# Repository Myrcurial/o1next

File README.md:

# o1next

> Rebuilding, upgrading, and eventually recreating the Osborne 1 — research,
> hardware, and the story of how this project began.

A general-purpose Z80 bus interposer for the Osborne 1, built around the RP2354B,
plus the research and reverse-engineering work it enables — and, downstream, a
modern-parts Osborne 1 reproduction (the "O1NEXT").

## The boards

**The shortform is the board's name** — its folder, its site URL and its board id
in `tools/check_schematics.py`. The register, with the state of each one, is
[`hardware/README.md`](hardware/README.md).

| Shortform | Board | Where |
|---|---|---|
| `floppy-adapter` | O1NEXT Floppy Adapter | [`hardware/floppy-adapter/`](hardware/floppy-adapter/) |
| `keyboard-adapter` | O1NEXT USB Keyboard Adapter | [`hardware/keyboard-adapter/`](hardware/keyboard-adapter/) |
| `wifi-comm-pac` | O1NEXT WiFi COMM PAC | [`hardware/wifi-comm-pac/`](hardware/wifi-comm-pac/) |
| `drive-c-repro` | O1NEXT Drive C Repro | [`hardware/drive-c-repro/`](hardware/drive-c-repro/) |
| `interposer-upgrade` | O1NEXT Upgrade — one board in four snap-off sections | [`hardware/interposer-upgrade/`](hardware/interposer-upgrade/) |
| `next-integrated` | O1NEXT Integrated — the SFF board | [`hardware/next-integrated/`](hardware/next-integrated/) |

`O1NEXT Complete` (the machine) is the `next-integrated` board with a case, a
screen, a battery pack and a keyboard — **hardware, but not a board**: chassis CAD,
print STLs, an assembly BOM and its own QMK / Cherry-MX keyboard, all in
`hardware/o1next-complete/`. An LFF 1:1 mainboard is *possible* if a chassis ever
needs restoring, and is not planned.

## What it does

The Osborne 1 places all peripherals in memory-mapped banks and the Z80 has a
simple, slow (4 MHz) external bus. A passive/active interposer in the Z80
socket, connected to an RP2354B, makes the machine both **observable** and
**extensible**:

| Personality | What it does | Code / issue |
|---|---|---|
| **Bus analyzer** (passive) | Cycle-accurate address/data/control capture, streamed over USB — the hardware equivalent of an emulator's machine-state view | `firmware/bus-analyzer/` #17 |
| **Peripheral synthesizer** (active) | Emulates period hardware on the same decode: RT-60A real-time clock, SCREEN-PAC 80/104-column video, IEEE-488 "Drive C" ramdisk/storage, CoPower-88 mailbox | `firmware/*` #18–#24 |
| **CPU emulation shim** | Virtual CoPower-88 (8088), so original SWP software runs on machines without the (rare) physical board | `firmware/copower88-shim/` #23 |
| **Floppy interposer** | Gotek/FlashFloppy analogue: interrupts the Shugart bus and mounts `.IMD`/`.HFE` images to either drive bay, or to "Drive C" as a persistent RAM disk | `firmware/floppy-emulator/` #20 |
| **WiFi modem** | Hayes-compatible AT command set + telnet, presented through the O1's memory-mapped 6850 ACIA registers so period comm programs work unchanged | `hardware/wifi-comm-pac/` #21, #56 |
| **Virtual printer** | Centronics-mode capture on the IEEE-488 port rendered to PDF, emulating a period 9-pin Epson MX-80 | `firmware/virtual-printer/` #19 |

The image library and the printer's PDFs are served by a C64 Ultimate-style
browser UI on the RP2354B, with a CP/M-side utility for in-machine control; no
local mods to the O1 are required (`firmware/web-ui/`).

Electrical/mechanical constraints and the settled design decisions live in
`hardware/README.md` and `firmware/README.md`; the bus and address-space
allocation is in `docs/virtual-peripherals-block-diagram.md`.

## Beyond the interposer — new peripherals for your Osborne 1

The interposer is the centre of the project, but it is not the only way to add
modern capability to the machine. **At least three standalone peripherals** do it
with no interposer, no BIOS change, and nothing cut:

- **USB keyboard adapter (#47)** — RP2040 board on the P4 keyboard connector:
  plug in any USB HID keyboard, no other mods. `hardware/keyboard-adapter/`
- **Severable WiFi modem (#56, #21)** — ESP32 Zimodem fork (telnet + SSH) that
  hangs off the MODEM (P1) port, powers itself from the port, and needs no case
  opened. `hardware/wifi-comm-pac/`
- **Standalone Drive C reproduction (#84)** — RP2040 + flash on the IEEE-488 port
  (P3), powered from the P5 video connector, reproducing the machine's own RAM
  disk. `hardware/drive-c-repro/`

Each attaches to a port the machine already exposes, and each is reversible. The
USB keyboard adapter doubles as the matrix-injection firmware for the
interposer's web-KVM personality (#45).

**One power detail removes the only case-opening step in that list.** The
keyboard adapter's internal variant wants +12 V on P4 pin 19, which means
bridging J6 inside the machine. But the **MODEM port (P1, DE-9 pin 7) carries the
same +12 V through the same R21, and it is reachable without opening anything** —
so a **9-pin passthrough from the keyboard adapter to the modem port** can take
power from there instead. Nobody has to crack the case. Both loads share R21; the
current budget is deferred to `hardware/wifi-comm-pac/README.md`.

Downstream of all of it:

- **O1NEXT (#49, #52)** — modern-parts Osborne 1 reproduction running
  original ROMs and software. **Two boards:** an **LFF board**, a 1:1 mainboard
  replacement for a real **OCC1 or OCC1A** chassis (the restoration path), and an
  **SFF board**, fully integrated and deliberately *not* a 1:1 swap. **The O1NEXT is
  the SFF board with the rest of the machine wrapped around it** — a ~8 cm thick
  portable in O1A blue/grey with an 8" 1024×768 HDMI panel and USB-C PD / 18650
  power; the C64 Ultimate "Crystal" idea applied to an Osborne. `hardware/next-integrated/`
- **Osborne-side software** — MOUNT.COM (#27), FATCOPY (#51), the CoPower-88
  driver (#26) and an updated boot disk (#28): `software/README.md`.

## Status

Phase 0 (research and reverse-engineering, #1) is largely complete and Phase 1
(interposer hardware, #11) has begun — a Rev A schematic exists, but **no board
has been built or tested yet**, so everything downstream of the schematic is
still design work.

Status is deliberately *not* maintained in this file; a status list here goes
stale the day after it is written. The two live sources are:

- **`docs/research-gaps.md`** — every open question, where it stands, and what is
  left to close it.
- **the GitHub issues** — the work itself, one unit per issue, with the doc that
  will carry each result named up front.

The narrative version — how the research actually went, what was surprising, and
the machines it is about — lives on the [Project Blog](https://myrcurial.github.io/o1next/).

## Repository layout

| Path | Holds |
|---|---|
| `research/` | **Sources** — the archive: manuals, schematics, ROMs, disk images and machine photographs, each with recorded provenance (`research/README.md`) |
| `docs/` | **Conclusions** — what we worked out about the Osborne 1, one document per area; index and house style in `docs/README.md` |
| `hardware/` | Device definitions and KiCad projects — interposer, floppy adapter, keyboard adapter, WiFi modem module, O1NEXT (`hardware/README.md`) |
| `firmware/` | On-device firmware, one folder per interposer personality (`firmware/README.md`) |
| `software/` | Osborne-side CP/M software — MOUNT.COM, FATCOPY, CoPower-88 driver, boot disk (`software/README.md`) |
| `tools/` | Disk-image pipeline (TD0 → CP/M filesystem) and host-side analysis scripts (`tools/README.md`) |
| `site/` | The project blog — Jekyll source for GitHub Pages (`site/README.md`) |

## Sources

Full per-file provenance, with source URLs and the archive's licensing note, is
in `research/README.md`. In bulk the raw material comes from bitsavers, Don
Maslin's archive, Dave Dunfield's ImageDisk archive, Brett Hallen's `Osborne_1`
repository, and the Zorba and Kaypro communities.

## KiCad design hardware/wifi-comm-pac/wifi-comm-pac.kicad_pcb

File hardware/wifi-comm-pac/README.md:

# wifi-comm-pac — the O1NEXT WiFi COMM PAC (ESP32 Zimodem fork)

**Board:** `wifi-comm-pac` — the **O1NEXT WiFi COMM PAC** — the project's
**third deliverable**. See the register in [`../README.md`](../README.md).

A Hayes-compatible WiFi modem for the Osborne 1 that closely models the original
Osborne 1 COMM PAC 300-baud modem. It lives in the left-hand floppy storage pocket,
taking power and signal from the MODEM (P1) 9-pin port; the PCB also hosts eleven
indicator LEDs, a 15 × 11 mm speaker, the aux power port for the keyboard adapter,
and a USB-C port for programming or powering the ESP32.

**State: the Rev A schematic is captured; there is no PCB layout yet.**

It is **one design with two physical instantiations** — the standalone COMM PAC in
the machine's floppy pocket, and the same schematic copied onto the interposer and
the SFF board (#323). It is not a daughterboard: the interposer carries its own copy
of the circuit, and only the thing on the far end of GPIO15/16 differs.

Tracks: #56 (extension of #21). Physical interface documented by #57.

## Definition

- **Base:** Zimodem fork targeting **ESP32-S2** (not ESP8266, and not the C-series)
  — the S2 is the variant whose auto-baud pulse counter is **20-bit**, which is what
  makes the machine-side rate detection work at all (#317, #319); it carries the
  SSH client (`INCLUDE_SSH`), and the ESP8266 lacks the headroom entirely.
- **New O1-specific work on top:**
  1. **SSH as first-class transport** — keys, host verification, session
     management via the web UI; `ssh` from the O1 into a modern host.
  2. **Baud-rate buffering/correction** — decouple O1-side ACIA rate
     from the far-end link rate; makes the 2× business turbo (#55)
     usable and quietly corrects the factory 600/2400 → 650/2600 quirk.

## The MCU, the module, and the pin map

**ESP32-S2**, in an **`ESP32-S2-MINI-2U`** module — the **U** for its IPEX/U.FL
connector, which is what lets the antenna go on a pigtail to the case edge, away
from the floppy drives and the CRT (#56 §D).

That is the part Espressif still recommends rather than a preference: the
**MINI-1/MINI-1U are NRND**, and the **WROOM and SOLO/SOLO-U are end of life**
(2025-02-24 and 2024-09-05). The MINI-2 line is what is recommended for new designs.

**The pin map is [`pinmap.md`](pinmap.md)** — fourteen GPIO allocated, the other 23 of
the module's 37 deliberately left free, the panel and the four P1 handshake lines on
two I²C pins, and the fork's `#define` block written out in full. It is **one map for
both roles**: role A and role B differ only in what sits on the other end of
GPIO15/16 (#323).

## Host interface — MODEM port (P1): DE-9 pigtail, 2×5 IDC on the board

**The module does not plug into the machine.** The COMM-PAC sits in the
**left floppy pocket**, a short **10-conductor ribbon** leaves it, and a **DE-9
plug** on the far end goes into the machine's MODEM socket. The board end of
that ribbon is a **2×5 IDC header** — which is why the connector and its
orientation are ours, not inherited (#324). The manual describes it exactly:
*"plug the small, rectangular connector on the modem cable into the 10-pin
socket on the modem… grooved to fit only one way"* (`research/osborne1/Comm-Pac_Users_Manual.pdf`).

Ten conductors carry nine DE-9 signals plus one spare; the original modem used
only six of them (no CTS, no RI), and ours uses all of the status lines.

**TTL levels, not RS-232** — the port feeds the 6850 ACIA directly (status
`2A00H` / data `2A01H`), bypassing the level shifters.

| P1 | Signal | Level | Direction |
|---|---|---|---|
| 1 | GND | — | — |
| 2 | TXD | **5 V TTL** | O1 → module |
| 3 | — | not used | — |
| 4 | MSB | **open-collector** ("50 µA sink = inactive") | module → O1 |
| 5 | CTS | TTL | module → O1 |
| 6 | RXD | **bipolar, −0.5…−10 V = 1** | module → O1 |
| 7 | **+12.6 V DC** | labelled `VDD` in the Comm-Pac manual | power |
| 8 | MCB | TTL, low = suppress output | O1 → module |
| 9 | RI | TTL, falling edge sets the flag | module → O1 |

### The level stage — five signal paths, three part types

**5 V TTL is not 3.3 V, and this board has to say so.** The 6850 and the PIA are
+5 V parts, so TXD and MCB arrive as a 0–5 V swing. The ESP32-S2's input limit
is `VDD + 0.3` — it is **not 5 V tolerant** — so every path below needs level work,
in both directions.

| Path | Part | Why |
|---|---|---|
| TXD, MCB (5 V → 3.3 V) | **74LVC4T245** | dual-supply translator, 5 V-tolerant B side |
| CTS, RI (3.3 V → 5 V) | **74LVC4T245** | the second 4-bit half; one `DIR` per package, so mixed directions cost two packages, not one |
| MSB (3.3 V → open-collector) | **74LVC1G07** | open-drain, 5 V-tolerant output; a push-pull driver would violate the interface |
| RXD (3.3 V → bipolar) | **MAX3232 at 3.3 V** | on-chip charge pump gives **±5.5 V**, inside the machine's −0.5…−10 V window and under the 5.1 V clamp; at 5 V it would swing ±9–10 V, needlessly close to both limits |

The MAX3232's receivers are RS-232-threshold and must **not** be used for the
TTL lines. Its 3.3 V rail is taken **after** the diode-OR, so an unpowered board
can never drive the machine's RXD.

Still to confirm in hardware: the **RXD negative swing**, on a real machine (#324).

## Power

**DE-9 pin 7 is +12.6 V DC, and it is behind the 22 Ω.** The Technical Manual
§4.3.2 says so in words — "7 +12v — Connected to power supply through 22 ohms" —
and sheet 7 of 9 shows the arrangement: `R21 = 22 Ω` hangs off the `+12V` rail and
its lower end is a junction feeding **both** P1 pin 7 and **`J6 pin 1 → J6 pin 2
→ P4-19`**, the keyboard branch.

The sheet labels that node `+12V`, which is what makes this easy to get wrong:
old schematics name a current-limited net after the rail it comes from, so **the
series part sits upstream of the label, and a net label does not tell you where
it is**. A 600 dpi read of the sheet alone does not settle it; the manual is the
tie-breaker, and it says *through 22 ohms*.

**That makes the port current limited, and the limit is the resistor's own rating.**
The sheet's default is **1/4 W** and nothing calls `R21` out, so the continuous
budget is **~107 mA** — 2.35 V dropped, 10.25 V left at the module. (150 mA would
be 0.495 W, a 1/2 W part sitting *at* its rating.) The keyboard adapter (#47)
shares the resistor, so the budget is shared.

**Two ways to be powered, and the choice is open (#356):**

- **(a) Off P1's rail**, under that ~107 mA, with a **large bulk capacitor**
  carrying the burst power. Radio TX is very uneven — long idle, short spikes — so
  the cap supplies the peak and `R21` the average.
- **(b) Off the monitor jack (P5)**, essentially the way `drive-c-repro` will: that
  rail is **not limited** (#354), so the peaks stop being a design problem at the
  cost of a second cable and a shunt.

Either way the board needs a **front-panel interlink connector — a 2×2 keyed IDC
carrying 5 V, 12 V and ground** (`../README.md`, #356) — and a **cuttable trace on
its 12 V input**, so the same PCB is fed either from the machine's video port or
from the link. Its **interlink input is reverse-voltage protected**, and the **keyed
2-pin shroud is the 12 V source end**. If option (a) is refused, the modem
connector's **12 V pin is left disconnected** and the 12 V arrives over the link
instead.

- **Bulk capacitance is doing real work, not tidiness.** A WiFi TX burst is a few
  hundred mA; `R21` cannot supply that, so the capacitor supplies the peak and
  `R21` supplies the average. Size the cap from the burst energy, and check the
  average draw against the shared budget — with 22 Ω in the path there *is* an
  inrush and peak problem to design around.
- **Buck 12.6 V → 5 V**, then **5 V → 3.3 V**; USB-C VBUS is **5 V → 3.3 V only**.
  Two sources, **diode-OR** (Schottky pair, or a P-FET ideal diode if the drop
  matters) so neither back-feeds the other.
- **Switch ahead of the buck**, latching slide type, so "off" is genuinely dark.
  USB still runs the board with no machine attached (bench-prep, #207).
- The machine's `−12 V` rail is rated **0.1 A**; the negative rail for RXD comes
  from the MAX3232's own charge pump, never from the machine.

## Panel

**Eleven lamps and the handshake, on I²C — two AW9523B, split by function.**
U6 (`0x58`) carries the lamps; U7 (`0x59`) carries the four P1 handshake lines.
Both are fitted, because the handshake is not optional: 16 channels each, 5 and
12 spare respectively, and the pin argument is closed for good.

- 8 lamps on **P0** — push-pull, constant-current, per-LED dimming.
- 3 lamps on **P1** (TR, MR, RI) — **P1 is open-drain only** on this part, so
  those three get series resistors and sink from 3.3 V.
- The handshake sits on the 3.3 V side of the translators: CTS and RI out,
  MSB through the `1G07`, MCB in.

The expander **holds its outputs**, so a hung firmware leaves a readable frozen
panel rather than a dark one. Two **INTN** lines go to GPIO38 and GPIO21, and
`RESETN` is strapped with an RC (or shares one GPIO).

LED states and semantics are #322; current is set to **2–3 mA** per lamp.

## Audio

An **I²S-input class-D amplifier with its own DAC** (MAX98357A class) on the
**5 V** rail, three pins (BCLK/LRCLK/DIN) plus gain/mode straps, driving a
**real speaker** — not a piezo buzzer, and not an active buzzer. Both are the
wrong part: an active buzzer knows one note, and a bare piezo element is
non-linear and thin across the band, where the panel has to make **the noise a
modem makes**.

**J2 is Same Sky CMS-151103-088SP** — 15 × 11 × 3 mm rectangular frame, 0.7 W
(1.0 W max), **8 Ω**, PEEK cone, Nd-Fe-B magnet, solder-pad terminals. **8 Ω is the
only number that matters** — it is the load the MAX98357A wants — and the part is
small enough for the floppy-pocket envelope. Pin 1 is the **`+`** terminal (the
datasheet's polarity: the cone moves forward with positive dc on `+`), so it takes
`SPK_P`.

**Audio quality is explicitly not a requirement.** The panel is a noise generator:
it has to make dial tone, DTMF and a ring cadence, and nothing more. It runs in
**free air** in an unsealed case with a perforated front panel — no chamber, no
gasket, no port — and no response curve, resonance or SPL figure is designed
around. The datasheet's Fo and SPL are 1 cc-box measurements and are deliberately
not repeated here as if they described this board.

Its footprint is ours (`o1next:Speaker_SameSky_CMS-151103-088SP`), and its geometry
comes off the datasheet's mechanical drawing: the 15 × 11 × 3 mm body, and **two
0.6 mm square solder pads on the left and right sides**. They are drawn 14.4 mm
apart, with each pad's outer edge flush with the 15 mm body end — that flush
offset is the one number read rather than stated, and it is what would change if
the drawing insets them. **The piezo route is closed, not deferred:** the Multicomp
Pro MCKPT-G1340-3917 buzzer is not fitted, and its footprint is not on the board.

Dial tone, DTMF and ring cadence are in #322; prior art is `na103/zimodem`
(CC BY 4.0 — method only).

## The schematic — two directories

**Two directories, and the generator writes into only one of them.**

| | |
|---|---|
| `wifi-comm-pac-generated/` | the generator's output. Regenerated at will. |
| `wifi-comm-pac-edited/` | the copy a person works on. Never written by the generator. |

`gen_wifi_comm_pac_sch.py` is the **first take** — the mathematical proof that the
circuit is what the netlist says it is. It is not a finished drawing and it cannot
be one: turning it into something a person can read and work on takes a person.
So both exist, and the rule between them is one line:

> if `-edited/` holds a schematic, **the copy is aborted** and the generator says
> so; if `-edited/` is empty, the generated schematic is copied across.

A regeneration therefore cannot overwrite anybody's work, and the first person to
pick the board up gets a starting point without running anything. To deliberately
re-seed, empty `-edited/` first — which discards what is in it.

`tools/check_schematics.py` asserts the **generated** file: the invariant nets
(which P1 pin carries which signal, that the machine's 5 V never reaches a 3.3 V
pin, that the 12.6 V rail stops at the buck), that no symbol or label collides,
that no symbol pin is without a footprint pad, and that the file matches a fresh
regeneration.

### Four sections, and parts sit next to what they connect to

The sheet is A1 (841 × 594 mm) divided into four regions, because the complaint a
reader actually has is not that things are unconnected — it is that they are
connected *across the page* and so cannot be followed:

| Section | Holds |
|---|---|
| **POWER** (bottom band) | the P1 12.6 V rail and the USB-C front end — diode-OR, buck, LDO, polyfuse, the CC pulldowns, the ESD clamp, and the 5 V out |
| **LOGIC** (left, upper) | J1, the level stage, the ESP32 and its support parts, both expanders, and the free-GPIO header |
| **PANEL** (right, upper) | the 11 lamps, one row each: resistor and LED side by side |
| **AUDIO** (right, lower) | the MAX98357A and the speaker |

### The free-GPIO header, J4 — and why it is 2×13

U5 leaves **26 GPIO** unused. No-connect is correct but *terminal*: the pad is on
the module's footprint, the header is not, and reaching it later means redoing the
board. **J4** brings all 26 out to a **2×13 header** — 2×13 exactly, because that
is the 26 GPIO and not 2×14 with grounds.

**It is left unpopulated, and marked `dnp`** so KiCad keeps it out of the BOM and
off the placement file. That is the difference between "left unfitted on purpose"
and "we forgot to order it". The pads cost nothing and mean somebody can solder a
header on later and use the radio, the DACs, the touch channels and the second SPI
set without touching U5's footprint.

Pins are numbered the way a 2×13 is — odd on row 1, even on row 2 — and **named
with the module's own IO names**, so the silk says `IO43` and that is UART0 TXD
without a datasheet lookup:

| | row 1 (odd) | row 2 (even) |
|---|---|---|
| | IO0 IO1 IO2 IO3 IO4 IO5 IO6 IO7 IO8 IO9 IO10 IO11 IO12 | IO13 IO14 IO17 IO18 IO26 IO39 IO40 IO41 IO42 IO43 IO44 IO45 IO46 |

One table in the generator builds U5's symbol, names these nets, *and* labels the
header, and `check_schematics.py` asserts each of the 26 as an **exact pair** — one
U5 pad and one J4 pin. Three separate lists would drift, and the first thing to
drift would be a header pin labelled `IO18` that is really `IO17`, which is the
worst possible bug on a header a hobbyist is meant to use.

### 5 V out to the keyboard adapter

**J5** is a **JST PH, side entry, SMD** (`S2B-PH-SM4-TB`). It is fully shrouded
with a polarising slot, so the plug cannot go in the wrong way round and **there is
no reverse-voltage case to design for**. Side entry means the cable leaves parallel
to the board, straight out the front of the floppy pocket. 2 A, 100 V, 2.0 mm
pitch; KiCad carries the footprint, so nothing is drawn here.

It is fed from the **diode-OR output** (`+5V`), so whichever source is present —
the machine's 12.6 V through the buck, or USB VBUS — feeds the port. That is what
lets the keyboard adapter drop its 12 V→5 V buck and keep only its LDO.

**U11 is the current limit on it.** `D13`/`D14` are SS14 — **1 A each** — so the
5 V rail cannot source more than about an amp, and a port labelled "5 V out"
invites somebody to plug in a load that wants three. `U11` is a **TPS2553**
current-limited power-distribution switch, and `R28` sets the limit: `I_OS = 25.6 /
R_ILIM`, so **27 kΩ gives about 0.95 A** — under the diodes, and 15× the ~60 mA the
adapter draws. It limits rather than latches, so nothing needs to know when it
does; `FAULT` is unused for that reason.

### ESD on the USB-C input

**`D15`** is a `PESD5V0S1BA` on `VBUS_IN`, upstream of the diode-OR, so it is the
first thing a transient meets. 5 V standoff, so it does not conduct on a 5.25 V
VBUS, and it clamps low enough not to overstress the `AP2112K` downstream. The
port is *meant* for a computer; "meant for" is not a protection.

### The wiring, and the defect it fixes

Every signal net is drawn as orthogonal wire segments; the rails use power
symbols; every pin ends on a wire, a power symbol, or a deliberate no-connect
marker. Nothing floats — the generator fails loudly if a pin does.

The router builds a **spanning tree** per net (each pin joined to the nearest
point already on the net, so branches share a trunk) and then **normalises** the
result: every segment is split wherever any point of the same net lies on it, the
duplicates that leaves are dropped, and a junction is placed wherever three or
more wire ends meet.

That normalisation is not cosmetic, and it is the answer to a real failure. The
earlier **star** router drew each pin back to the first pin, which produced
**overlapping collinear segments** — 15 of them, plus 2 exact duplicates. KiCad
tolerates that until it saves the file, at which point its own cleaner normalises
the geometry, and pins that had been attached *only* by sitting inside an overlap
come adrift, because a pin in the middle of a wire is not connected without a
junction. That cost **14 pins across 10 nets** the first time anybody opened the
sheet in KiCad. **A wire KiCad would rewrite is a wire drawn wrong**, so the
generator now does the normalisation itself.

It is checked, not asserted: `kicad-cli sch upgrade` re-saves the schematic in the
current format — the operation that detaches pins from an overlapping drawing — and
the netlist before and after is identical (70 nets, 248 nodes, 0 single-node nets,
317 wires and 8 junctions unchanged).

```sh
python3 hardware/wifi-comm-pac/gen_wifi_comm_pac_sch.py
python3 tools/check_schematics.py --board wifi-comm-pac
```

| Ref | Part | Why |
|---|---|---|
| J1 | 2×5 IDC | the P1 pigtail; pin *n* = DE-9 pin *n* |
| U1, U2 | 74LVC4T245 | 5 V ↔ 3.3 V, one package per direction |
| U3 | 74LVC1G07 | MSB, open-drain only |
| U4 | MAX3232 | RXD, bipolar, on 3.3 V |
| U5 | ESP32-S2-MINI-2U | the modem |
| U6, U7 | AW9523B ×2 | panel (0x58) and handshake (0x59) |
| U8 | MAX98357A | I²S class-D audio |
| U9, U10 | TPS54331, AP2112K | 12.6 V → 5 V → 3.3 V |
| D13, D14 | Schottky pair | the diode-OR between the port and USB |

**Footprints are all assigned** — **71 of 71** component symbols carry one, so
`Update PCB from Schematic` transfers every part rather than nothing.

**But the board is not yet correct, and this is the first layout task.** The
**multi-pin ICs' pin numbers are logical placeholders**, not the vendor packages'.
They exist so the netlist checker can name a pin. The footprints are real; the
pin↔pad correspondence is not. **U5 is the dangerous one:** its symbol has 18
pins numbered 1–18, the `ESP32-S2-MINI-2U` footprint has 73 pads numbered 1–65
plus `61_1`…`61_9`, and the numbers *collide by name* while disagreeing in
meaning — symbol pin 1 is `+3V3`, the module's pin 1 is **`GND1`**. So a transfer
today puts 3.3 V on a ground pad. The other multi-pin parts are merely incomplete
rather than wrong: U1/U2 (9 pins against 16 pads, two of four channels modelled),
U8 (9 against 17), U3 (5 against 6), U6/U7 (24 against 25 — pad 25 is the exposed
pad), SW1 (2 against 7 — the five mounting tabs). U4, U9 and U10 are exact.

**J3 is the exception** that shows the fix: it uses the part's own numbers
(A1–A12, B1–B12, SH1–SH6) because its footprint has 30 pads and every one of them
needed a net. Doing the same for the others means binding each signal to a real
module pin, which is a **GPIO allocation decision** for U5 rather than a datasheet
lookup.

The RXD swing is the remaining hardware confirmation (#324), and the **2×5 IDC
orientation is settled** — see `pinmap.md` §"Open before layout": right-angle and
shrouded, pin 1 on the left facing it, key down toward the PCB.

## Enclosure

The case STL is **already designed and fit-tested** by the maintainer; the
apertures it currently cuts are **USB-C** and the **2×5 IDC**. Final placement,
left to right looking at the front of the machine:

1. **antenna connector** — RP-SMA bulkhead (reverse-polarity, as every WiFi
   pigtail is; the module end is U.FL), fed from the MINI-2U's IPEX connector
2. **power switch**
3. **2×5 IDC** — the P1 ribbon
4. **LED row** — 11 × 3528 with light pipes
5. **USB-C**

The schematic fixes the parts; the placement drawing that goes with it is what
lets the STL be finalised (#56 §E).

## References

- `pinmap.md` — the MCU, the module, and every GPIO
- `docs/o1-modem-serial.md` (authoritative pinout + levels)
- `docs/o1-memory-io-map.md` §"6850 ACIA detail"
- `hardware/interposer-upgrade/` — the interposer the module docks to (#323)
- Upstream: https://github.com/bozimmerman/Zimodem

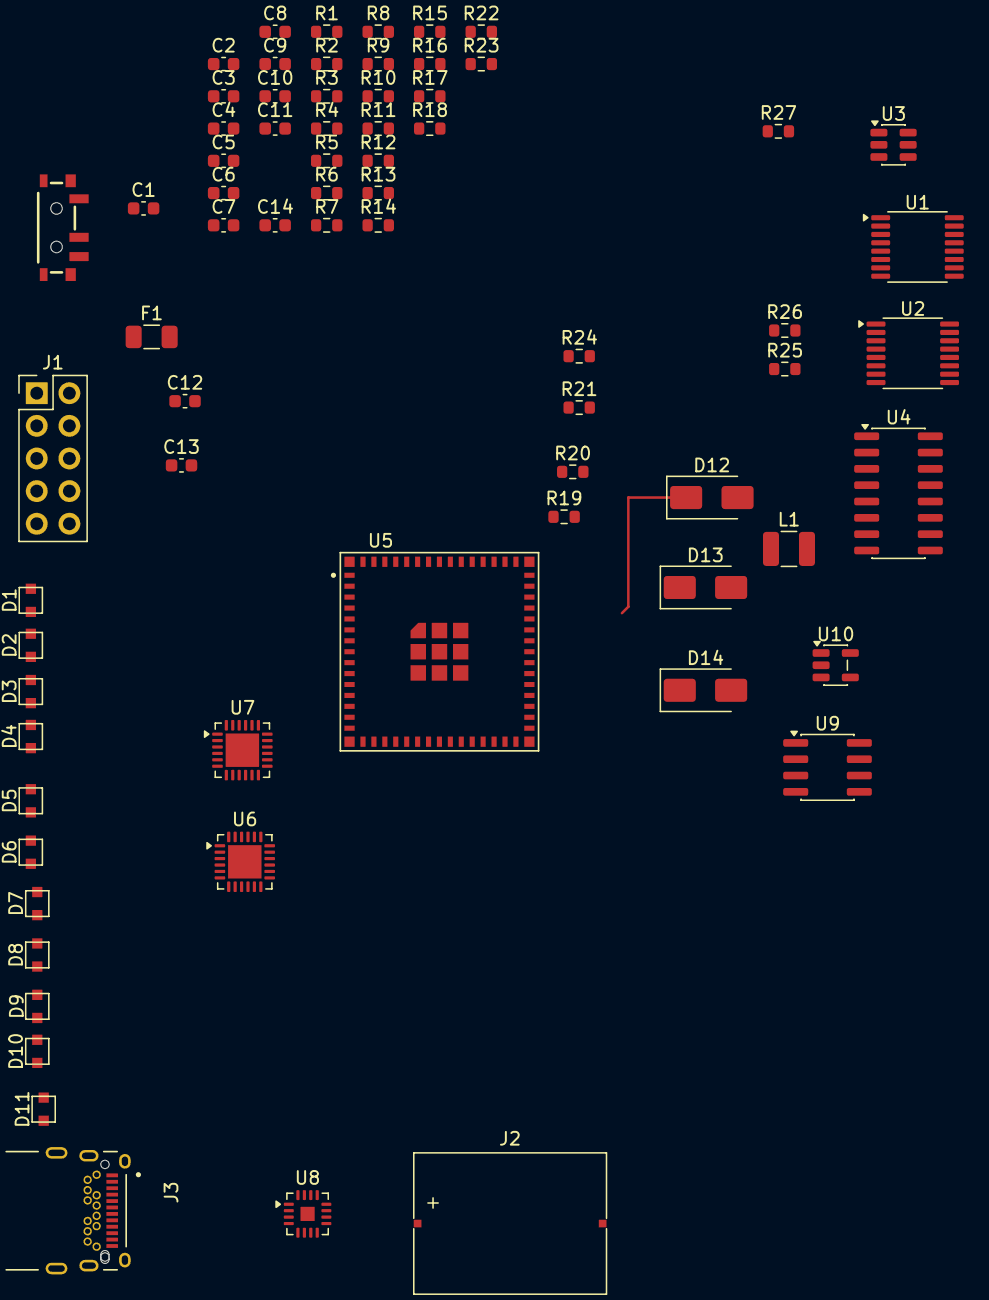
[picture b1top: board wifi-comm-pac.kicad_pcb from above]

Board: 2 copper layers, 71 parts (0 on the bottom side), 70 nets.

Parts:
C1: 220u; C_0603_1608Metric
C2, C8, C9, C10, C11, C12, C14: 100n; C_0603_1608Metric
C3: 10n; C_0603_1608Metric
C4: 1n; C_0603_1608Metric
C5, C6: 22u; C_0603_1608Metric
C7: 10u; C_0603_1608Metric
C13: 1u; C_0603_1608Metric
D1, D2, D3, D4, D5, D6, D7, D8, D9, D10, D11: 3528; LED_SunLED_XZM2CRK168WA
D12: SS34 catch; D_SMA
D13, D14: SS14 OR; D_SMA
F1: polyfuse 1A; Fuse_1206_3216Metric
J1: Conn_02x05 IDC (P1 MODEM); PinHeader_2x05_P2.54mm_Vertical
J2: CMS-151103-088SP; Speaker_SameSky_CMS-151103-088SP
J3: USB-C sink; USB_C_SameSky_UJ32-C-H-G-DSMT-1-P24-TR
L1: 10uH; L_1210_3225Metric
R1, R2, R3, R4, R5, R6, R7, R8, R9, R10, R11: 470R; R_0603_1608Metric
R12, R14, R19, R22, R23, R24, R25, R26, R27: 10k; R_0603_1608Metric
R13: 1k91; R_0603_1608Metric
R15, R16: 5k1; R_0603_1608Metric
R17, R18: 22R; R_0603_1608Metric
R20, R21: 4k7; R_0603_1608Metric
SW1: Slide switch, latching; Slide_SPST_SMD_6.7x2.6mm
U1: 74LVC4T245 (TXD/MCB); TSSOP-16_4.4x5mm_P0.65mm
U2: 74LVC4T245 (CTS/RI); TSSOP-16_4.4x5mm_P0.65mm
U3: 74LVC1G07 (MSB); SOT-23-6
U4: MAX3232 (RXD); SOIC-16_3.9x9.9mm_P1.27mm
U5: ESP32-S2-MINI-2U
U6: AW9523B panel 0x58; QFN-24-1EP_4x4mm_P0.5mm_EP2.6x2.6mm
U7: AW9523B interface 0x59; QFN-24-1EP_4x4mm_P0.5mm_EP2.6x2.6mm
U8: MAX98357A; VQFN-16-1EP_3x3mm_P0.5mm_EP1.1x1.1mm
U9: TPS54331 buck 12.6->5; SOIC-8_3.9x4.9mm_P1.27mm
U10: AP2112K-3.3 LDO; SOT-23-5

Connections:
+3V3: C7.1, C12.1, D9.1, D10.1, D11.1, R19.2 (2_2), R20.2 (2_2), R21.2 (2_2), R22.2, R23.2, R24.2 (2_2), R25.2, R26.2, R27.2, U1.1 (VCCA), U2.1 (VCCA), U2.7 (DIR), U3.5 (VCC), U4.16 (VCC), U5.1 (3V3), U6.1 (VDD), U7.1 (VDD), U7.5 (AD0), U8.6 (SD_MODE), U10.4 (VOUT)
+5V: C6.1, D13.2, D14.2, U1.13 (VCCB), U2.13 (VCCB), U8.1 (VDD), U10.1 (VIN), U10.3 (EN)
+5V_P1: C5.1, D13.1, L1.2, R12.1 (1_1)
+5V_USB: D14.1, F1.2
+12V: J1.7 (+12.6V), SW1.1
+12V_SW: C1.1, SW1.2, U9.2 (VIN), U9.3 (EN)
/BOOT_N: C2.1, U9.1 (BOOT)
/C1N: C8.2, U4.3 (C1-)
/C1P: C8.1, U4.1 (C1+)
/C2N: C9.2, U4.5 (C2-)
/C2P: C9.1, U4.4 (C2+)
/COMP_N: R14.1, U9.6 (COMP)
/ESP_EN: C13.1, U5.3 (EN)
/EXP_RSTN: C14.1, U7.8 (RESETN)
/FB_N: R13.1, U9.5 (VSENSE)
/I2C_SCL: U6.4 (SCL), U7.4 (SCL)
/I2C_SDA: U6.3 (SDA), U7.3 (SDA)
/I2S_BCLK: U5.9 (IO35), U8.3 (BCLK)
/I2S_DIN: U5.11 (IO37), U8.5 (DIN)
/I2S_LRCLK: U5.10 (IO36), U8.4 (LRCLK)
/IF_CTS: R25.1, U2.3 (A1), U7.9 (P1_0)
/IF_MSB: R27.1, U3.2 (A)
/IF_RI: R26.1, U2.4 (A2)
/INT_IF: R23.1, U7.7 (INTN)
/INT_PANEL: R22.1, U5.12 (IO38)
/LED_AA: R4.1, U6.20 (P0_3)
/LED_AA_A: D4.1, R4.2
/LED_CD: R5.1, U6.21 (P0_4)
/LED_CD_A: D5.1, R5.2
/LED_CONN: R2.1, U6.18 (P0_1)
/LED_CONN_A: D2.1, R2.2
/LED_HS: R3.1, U6.19 (P0_2)
/LED_HS_A: D3.1, R3.2
/LED_MR_A: D10.2, R10.2
/LED_MR_K: R10.1, U6.10 (P1_1)
/LED_OH: R6.1, U6.22 (P0_5)
/LED_OH_A: D6.1, R6.2
/LED_RADIO: R1.1, U6.17 (P0_0)
/LED_RADIO_A: D1.1, R1.2
/LED_RD: R7.1, U6.23 (P0_6)
/LED_RD_A: D7.1, R7.2
/LED_RI_A: D11.2, R11.2
/LED_RI_K: R11.1, U6.11 (P1_2)
/LED_SD: R8.1, U6.24 (P0_7)
/LED_SD_A: D8.1, R8.2
/LED_TR_A: D9.2, R9.2
/LED_TR_K: R9.1, U6.9 (P1_0)
/O1_MCB_3V3: U1.4 (A2), U7.12 (P1_3)
/O1_TXD_3V3: U1.3 (A1), U5.6 (IO16)
/P1_CTS: J1.5 (CTS), U2.8 (B1)
/P1_MCB: J1.8 (MCB), U1.9 (B2)
/P1_MSB: J1.4 (MSB), U3.4 (Y)
/P1_RI: J1.9 (RI), U2.9 (B2)
/P1_RXD: J1.6 (RXD), U4.14 (T1OUT)
/P1_TXD: J1.2 (TXD), U1.8 (B1)
/PH_N: C2.2, D12.2, L1.1, U9.8 (PH)
/SPK_N: J2.2, U8.9 (OUT-)
/SPK_P: J2.1, U8.8 (OUT+)
/SS_N: C3.1, U9.4 (SS)
/UART1_TX: U4.11 (T1IN), U5.5 (IO15)
/USB_CC1: J3.A5 (CC1), R15.1
/USB_CC2: J3.B5 (CC2), R16.1
/USB_DM_CON: J3.A7 (DN1), J3.B7 (DN2), R18.2
/USB_DM_ESP: R18.1, U5.14 (IO19)
/USB_DP_CON: J3.A6 (DP1), J3.B6 (DP2), R17.2
/USB_DP_ESP: R17.1, U5.15 (IO20)
/VBUS_IN: F1.1, J3.A4 (VBUS), J3.B9 (VBUS)
/VN: C11.1, U4.6 (V-)
/VP: C10.1, U4.2 (V+)
GND: C1.2, C3.2, C4.2 (2_2), C5.2, C6.2, C7.2, C10.2, C11.2, C12.2, C13.2, C14.2, D1.2, D2.2, D3.2, D4.2, D5.2, D6.2, D7.2, D8.2, D12.1, J1.1 (GND), J3.A1 (GND), J3.A12 (GND), J3.B1 (GND), J3.B12 (GND), J3.SH1 (SHIELD), J3.SH2 (SHIELD), J3.SH3 (SHIELD), J3.SH4 (SHIELD), J3.SH5 (SHIELD), J3.SH6 (SHIELD), R13.2, R14.2, R15.2, R16.2, U1.2 (GND), U1.7 (DIR), U1.12 (/OE), U2.2 (GND), U2.12 (/OE), U3.3 (GND), U4.8 (R2IN), U4.10 (T2IN), U4.13 (R1IN), U4.15 (GND), U5.2 (GND), U5.18 (GND), U6.2 (GND), U6.5 (AD0), U6.6 (AD1), U7.2 (GND), U7.6 (AD1), U8.2 (GND), U8.7 (GAIN), U9.7 (GND), U10.2 (GND)

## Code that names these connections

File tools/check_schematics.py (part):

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    # other.  It moves whenever a part is added, which is why the derivation is
    # written down rather than the number.
    erc_allowance={"lib_symbol_issues": 189},
    pinout=[("J1", {1: "GND", 2: "P1_TXD", 4: "P1_MSB", 5: "P1_CTS",
                    6: "P1_RXD", 7: "+12V", 8: "P1_MCB", 9: "P1_RI"})],
    exact_nets={
        "P1_TXD": {("J1", "2"), ("U1", "8")},
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

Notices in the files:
parts and their libraries:
SparkFun COM-10860 Surface Mount Right Angle Switch, SPST, 6.7 x 2.6 mm. Copied from github.com/sparkfun/SparkFun-KiCad-Libraries, which is CC BY 4.0 -- attribution is the licence. Upgraded to the current KiCad format and kept here so the board needs no external library. o1next issue #324.
